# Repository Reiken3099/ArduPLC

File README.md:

# ArduPLC

PCB board designs developed with the purpose of being used as an alternative to the widely known PLCs in industrial environments, focusing on keeping these PCB boards as closely attached to what is currently used in the industry in terms of voltages and currents. This project does not seek in any way to replace the use of PLC devices in the industry or any related element, it is developed with the sole purpose of having a reliable and low-cost alternative to such devices, mainly for small or micro companies that require a considerable degree of automation keeping your costs and expenses as low as possible.

These boards base their operation on the ATMEL microcontrollers used in the Arduino boards, for which these can be programmed in a simple and intuitive way using the Arduino IDE software, loading the bootloader of the corresponding Arduino boards in these microcontrollers, or failing that as well They can be programmed using assembly language or C ++ and programmed with the help of a microcontroller recorder or charger. Any PCB board shown here was designed to be used with the Arduino bootloader, since by including this, you can use the program free software called "LDmicro", through which you can program ATMEL microcontrollers with the Arduino bootloader using the LADDER language or also known as the ladder language, the same language that is used to program PLC devices today.

This is a project that is currently under development, so the plates shown here have not yet been polished in terms of design and structure of their components, however, each one is fully functional and has been physically and different simulations.

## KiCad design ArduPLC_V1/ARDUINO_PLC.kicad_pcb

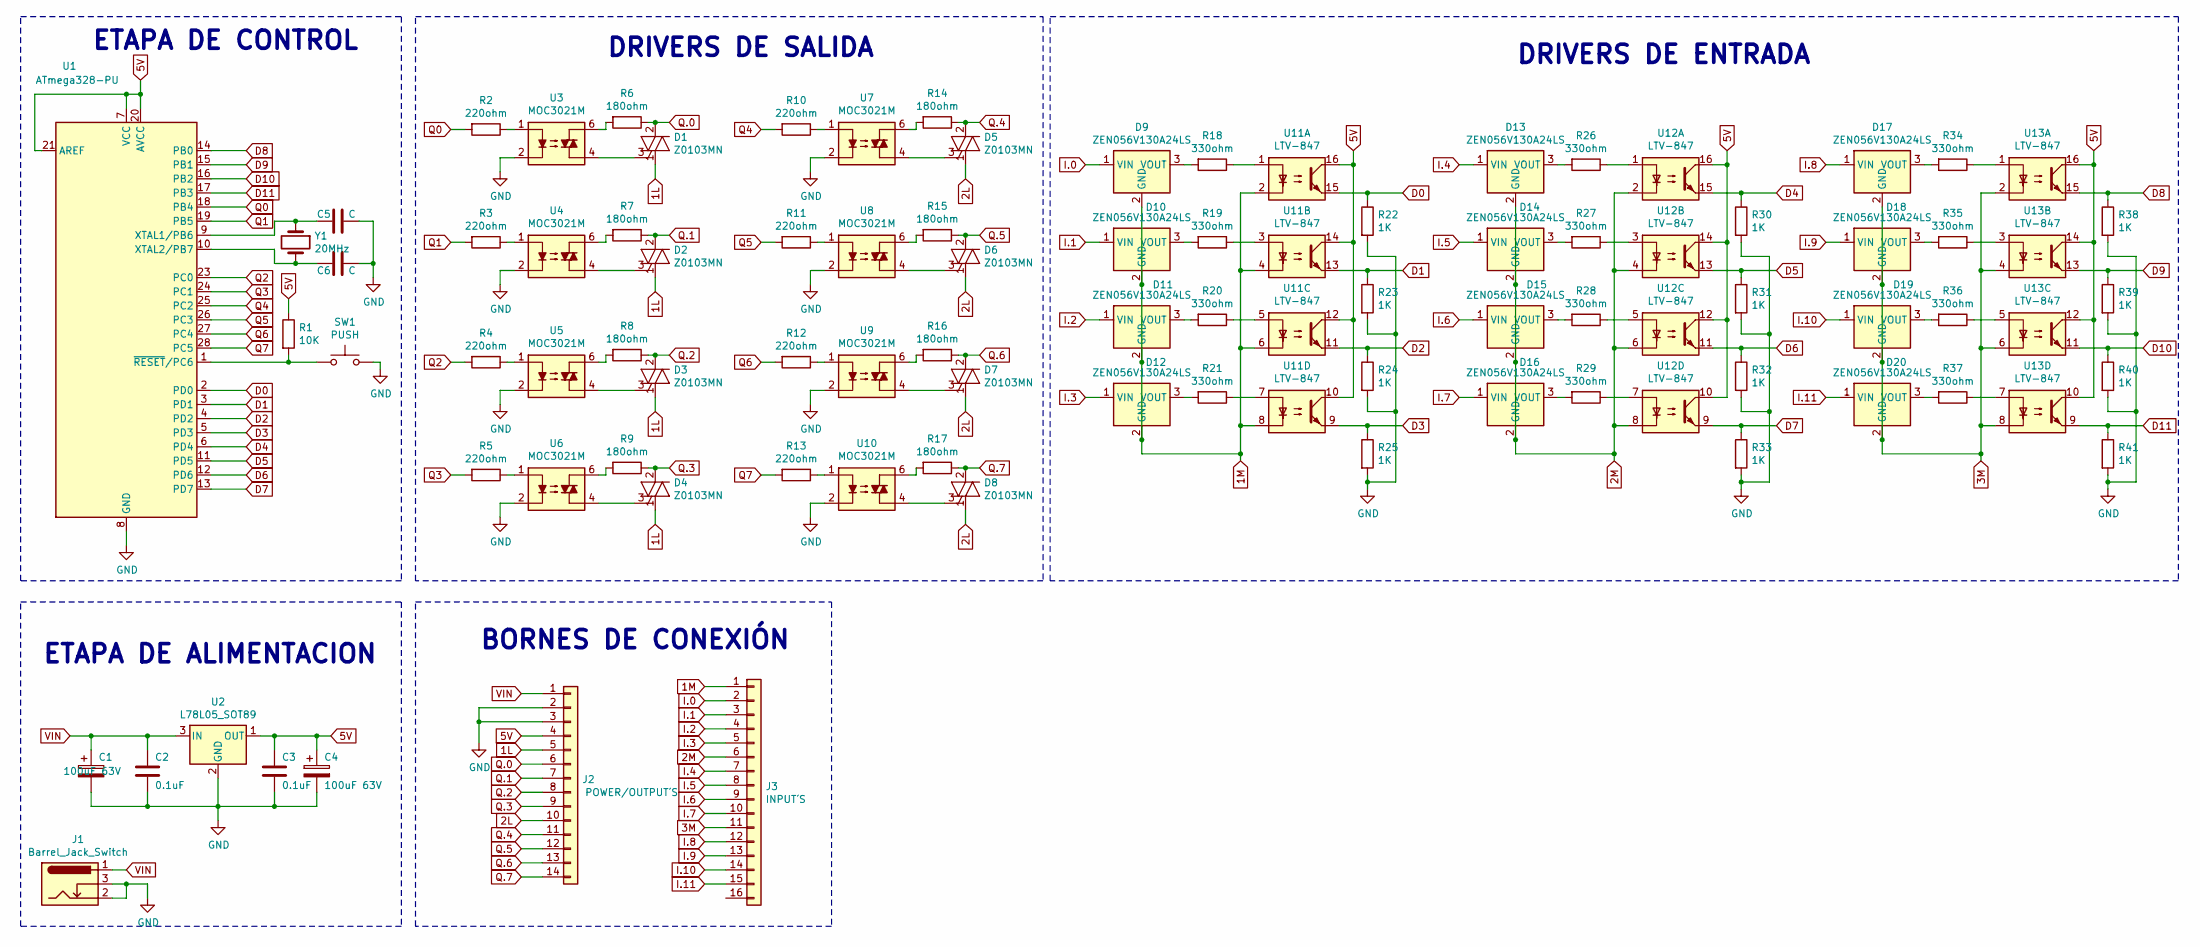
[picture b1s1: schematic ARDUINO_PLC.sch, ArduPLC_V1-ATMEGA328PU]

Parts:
C1, C4: 100uF 63V; CP_Radial_D8.0mm_P3.80mm
C2, C3: 0.1uF; C_Disc_D5.0mm_W2.5mm_P2.50mm
C5, C6: C; C_Disc_D5.0mm_W2.5mm_P2.50mm
D1, D2, D3, D4, D5, D6, D7, D8: Z0103MN; SOT-223
D9, D10, D11, D12, D13, D14, D15, D16, D17, D18, D19, D20: ZEN056V130A24LS; Littelfuse_PolyZen-LS
J1: Barrel_Jack_Switch; BarrelJack_Horizontal
J2: POWER/OUTPUT´S; Altech_AK300_1x14_P5.00mm_45-Degree
J3: INPUT´S; Altech_AK300_1x16_P5.00mm_45-Degree
R1: 10K; R_Axial_DIN0204_L3.6mm_D1.6mm_P1.90mm_Vertical
R2, R3, R4, R5, R10, R11, R12, R13: 220ohm; R_Axial_DIN0204_L3.6mm_D1.6mm_P1.90mm_Vertical
R6, R7, R8, R9, R14, R15, R16, R17: 180ohm; R_Axial_DIN0204_L3.6mm_D1.6mm_P1.90mm_Vertical
R18, R19, R20, R21, R26, R27, R28, R29, R34, R35, R36, R37: 330ohm; R_Axial_DIN0204_L3.6mm_D1.6mm_P1.90mm_Vertical
R22, R23, R24, R25, R30, R31, R32, R33, R38, R39, R40, R41: 1K; R_Axial_DIN0204_L3.6mm_D1.6mm_P1.90mm_Vertical
SW1: PUSH; Button_6mm
U1: ATmega328-PU; DIP-28_W7.62mm
U2: L78L05_SOT89; SOT-89-3
U3, U4, U5, U6, U7, U8, U9, U10: MOC3021M; DIP-6_W7.62mm_LongPads
U11, U12, U13: LTV-847; DIP-16_W7.62mm
Y1: 20MHz; Crystal_HC52-U_Vertical

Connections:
1L: D1.1 (A1), D2.1 (A1), D3.1 (A1), D4.1 (A1), J2.5
1M: D9.2 (GND), D10.2 (GND), D11.2 (GND), D12.2 (GND), J3.1, U11.2, U11.4, U11.6, U11.8
2L: D5.1 (A1), D6.1 (A1), D7.1 (A1), D8.1 (A1), J2.10
2M: D13.2 (GND), D14.2 (GND), D15.2 (GND), D16.2 (GND), J3.6, U12.2, U12.4, U12.6, U12.8
3M: D17.2 (GND), D18.2 (GND), D19.2 (GND), D20.2 (GND), J3.11, U13.2, U13.4, U13.6, U13.8
5V: C3.1, C4.1, J2.4, R1.1, U1.7 (VCC), U1.20 (AVCC), U1.21 (AREF), U2.1 (OUT), U11.10, U11.12, U11.14, U11.16, U12.10, U12.12, U12.14, U12.16, U13.10, U13.12, U13.14, U13.16
D0: R22.1, U1.2 (PD0), U11.15
D1: R23.1, U1.3 (PD1), U11.13
D2: R24.1, U1.4 (PD2), U11.11
D3: R25.1, U1.5 (PD3), U11.9
D4: R30.1, U1.6 (PD4), U12.15
D5: R31.1, U1.11 (PD5), U12.13
D6: R32.1, U1.12 (PD6), U12.11
D7: R33.1, U1.13 (PD7), U12.9
D8: R38.1, U1.14 (PB0), U13.15
D9: R39.1, U1.15 (PB1), U13.13
D10: R40.1, U1.16 (PB2), U13.11
D11: R41.1, U1.17 (PB3), U13.9
GND: C1.2, C2.2, C3.2, C4.2, C5.1, C6.1, J1.2, J1.3, J2.2, J2.3, R22.2, R23.2, R24.2, R25.2, R30.2, R31.2, R32.2, R33.2, R38.2, R39.2, R40.2, R41.2, SW1.2, U1.8 (GND), U1.22 (GND), U2.2 (GND), U3.2, U4.2, U5.2, U6.2, U7.2, U8.2, U9.2, U10.2
I.0: D9.1 (VIN), J3.2
I.1: D10.1 (VIN), J3.3
I.2: D11.1 (VIN), J3.4
I.3: D12.1 (VIN), J3.5
I.4: D13.1 (VIN), J3.7
I.5: D14.1 (VIN), J3.8
I.6: D15.1 (VIN), J3.9
I.7: D16.1 (VIN), J3.10
I.8: D17.1 (VIN), J3.12
I.9: D18.1 (VIN), J3.13
I.10: D19.1 (VIN), J3.14
I.11: D20.1 (VIN), J3.15
unnamed: C5.2, U1.9 (XTAL1/PB6), Y1.1
unnamed: C6.2, U1.10 (XTAL2/PB7), Y1.2
unnamed: D1.3 (G), U3.4
unnamed: D2.3 (G), U4.4
unnamed: D3.3 (G), U5.4
unnamed: D4.3 (G), U6.4
unnamed: D5.3 (G), U7.4
unnamed: D6.3 (G), U8.4
unnamed: D7.3 (G), U9.4
unnamed: D8.3 (G), U10.4
unnamed: D9.3 (VOUT), R18.2
unnamed: D10.3 (VOUT), R19.2
unnamed: D11.3 (VOUT), R20.2
unnamed: D12.3 (VOUT), R21.2
unnamed: D13.3 (VOUT), R26.2
unnamed: D14.3 (VOUT), R27.2
unnamed: D15.3 (VOUT), R28.2
unnamed: D16.3 (VOUT), R29.2
unnamed: D17.3 (VOUT), R34.2
unnamed: D18.3 (VOUT), R35.2
unnamed: D19.3 (VOUT), R36.2
unnamed: D20.3 (VOUT), R37.2
unnamed: R1.2, SW1.1, U1.1 (~RESET~/PC6)
unnamed: R2.1, U3.1
unnamed: R3.1, U4.1
unnamed: R4.1, U5.1
unnamed: R5.1, U6.1
unnamed: R6.2, U3.6
unnamed: R7.2, U4.6
unnamed: R8.2, U5.6
unnamed: R9.2, U6.6
unnamed: R10.1, U7.1
unnamed: R11.1, U8.1
unnamed: R12.1, U9.1
unnamed: R13.1, U10.1
unnamed: R14.2, U7.6
unnamed: R15.2, U8.6
unnamed: R16.2, U9.6
unnamed: R17.2, U10.6
unnamed: R18.1, U11.1
unnamed: R19.1, U11.3
unnamed: R20.1, U11.5
unnamed: R21.1, U11.7
unnamed: R26.1, U12.1
unnamed: R27.1, U12.3
unnamed: R28.1, U12.5
unnamed: R29.1, U12.7
unnamed: R34.1, U13.1
unnamed: R35.1, U13.3
unnamed: R36.1, U13.5
unnamed: R37.1, U13.7
Q0: R2.2, U1.18 (PB4)
Q1: R3.2, U1.19 (PB5)
Q2: R4.2, U1.23 (PC0)
Q3: R5.2, U1.24 (PC1)
Q4: R10.2, U1.25 (PC2)
Q5: R11.2, U1.26 (PC3)
Q6: R12.2, U1.27 (PC4)
Q7: R13.2, U1.28 (PC5)
Q.0: D1.2 (A2), D1.4 (A4), J2.6, R6.1
Q.1: D2.2 (A2), D2.4 (A4), J2.7, R7.1
Q.2: D3.2 (A2), D3.4 (A4), J2.8, R8.1
Q.3: D4.2 (A2), D4.4 (A4), J2.9, R9.1
Q.4: D5.2 (A2), D5.4 (A4), J2.11, R14.1
Q.5: D6.2 (A2), D6.4 (A4), J2.12, R15.1
Q.6: D7.2 (A2), D7.4 (A4), J2.13, R16.1
Q.7: D8.2 (A2), D8.4 (A4), J2.14, R17.1
VIN: C1.1, C2.1, J1.1, J2.1, U2.3 (IN)

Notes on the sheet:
ETAPA DE CONTROL
DRIVERS DE SALIDA
DRIVERS DE ENTRADA
ETAPA DE ALIMENTACION
BORNES DE CONEXIÓN

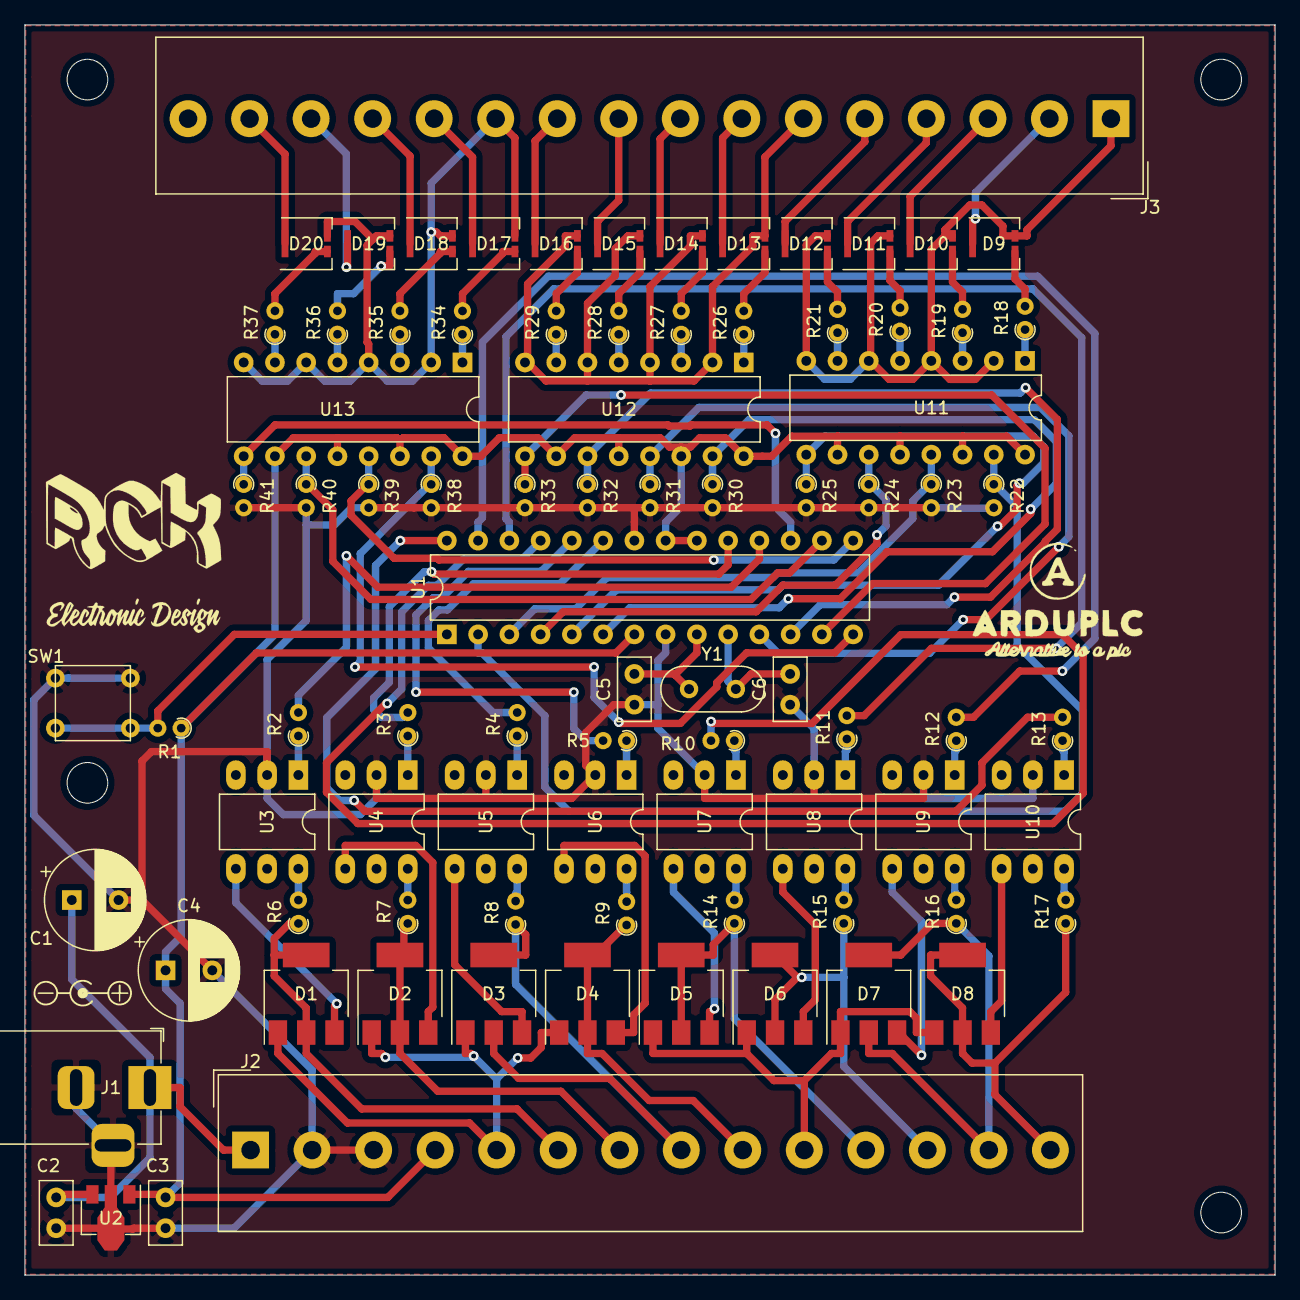
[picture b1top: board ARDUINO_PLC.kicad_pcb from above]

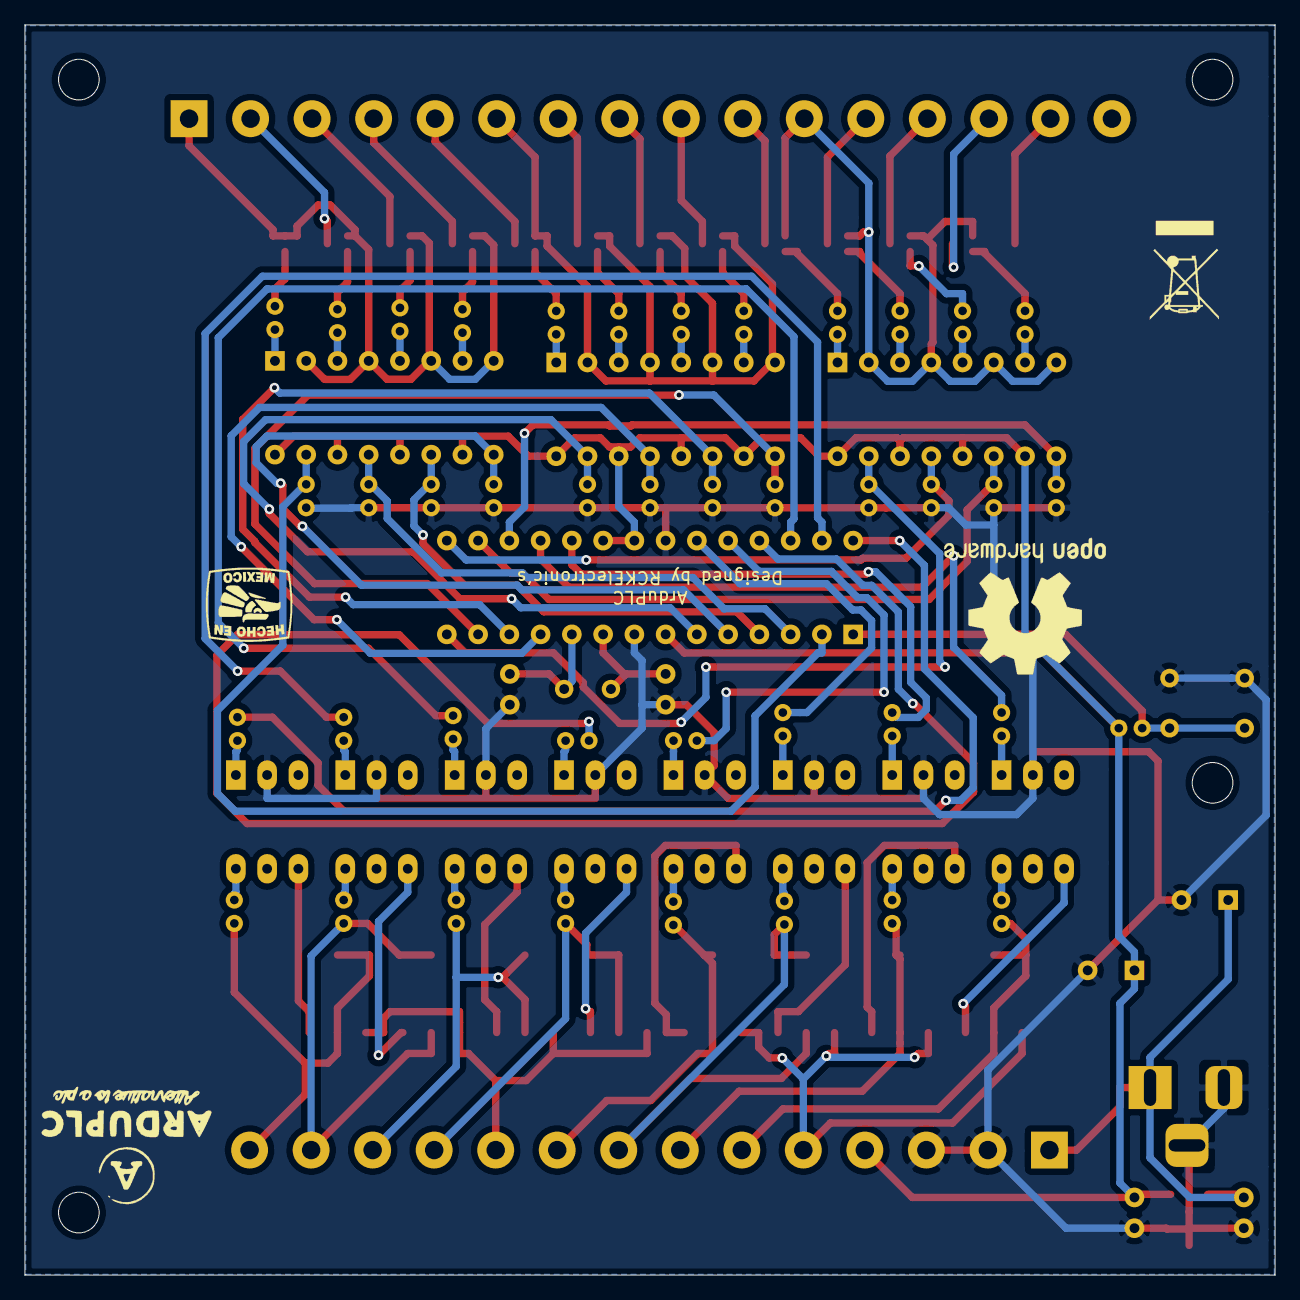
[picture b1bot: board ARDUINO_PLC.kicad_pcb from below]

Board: 2 copper layers, 101.6 x 101.6 mm, 89 parts (3 on the bottom side), 99 nets.

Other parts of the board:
G001: LOGO; echo_en_mexico
REF01: WEEE-Logo_5.6x8mm_SilkScreen
REF02: OSHW-Logo2_14.6x12mm_SilkScreen
REF03: Symbol_Barrel_Polarity
